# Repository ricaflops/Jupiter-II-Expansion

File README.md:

# Jupiter-II Expansion
An Expansion board for the [Jupiter-II](https://github.com/ricaflops/Jupiter-II) computer

## Expands Jupiter-II with
- Video color: 16 colors, RGB output
- Programmable Sound Generator
- 128K RAM: paged
- 16K ROM: FORTH vocabulary extension
- Serial Interface

## FORTH code examples

### Colors
```
CYAN BORDER ( Change screen border color )
WHITE PAPER ( Set char background color )
BLUE DARK INK ( Set char foreground color ) 

: COLORBAR
  CLS 10 8 AT 16 0
  DO
   I INK 144 EMIT
  LOOP 
  BLACK INK
  ;
COLORBAR ( Show a colorfull bar )
```

### Memory/Screen/Font Paging
```
0 FONT  ( select alternative character set )
1 FONT  ( select original character set )

0 SCREEN ( select screen page 0 )
1 SCREEN ( select screen page 1 )

0 MPAGE ( select memory page 0 )
3 MPAGE ( select memory page 3 )
```

### Sounds
```
: PING
  200 0 PSG!
  254 7 PSG!
  16 8 PSG!
  20 12 PSG!
  1 13 PSG!
;

: SHOT
  8 6 PSG!
  247 7 PSG!
  16 8 PSG!
  20 12 PSG!
  1  13 PSG!
;
```

### Serial Comm Port
8 data bits, 1 stop bit, no parity.
```
CREATE BUFFER 256 ALLOT ( Create and Allocate a memory space to work )
: CLRBUF BUFFER 256 32 FILL ; ( Clear Buffer )
: PRTBUF CR 256 0 DO BUFFER I + EMIT LOOP CR ; ( Print Buffer )

9600 BAUD     ( set communication baud rate )
CLRBUF        ( Clear Buffer )
BUFFER 256 RX ( Receive 256 bytes from serial line )
PRTBUF        ( View received data )
BUFFER 256 TX ( Transmit 256 bytes over serial line )
```
*Note: use Space key to abort communication if needed*

# Extra FORTH vocabulary
The extended vocabulary is copied from XROM to a unused 1K RAM area at $3000-$33FF of Jupiter-II during initialization.
That allows safe memory paging while keeping the extra Words accessible.

### Standard FORTH words

```
COUNT ( addr -- addr+1 c )  Extract String length
+! ( n addr -- )  Add 'n' to 'addr' variable
? ( addr -- )  Print variable value
CMOVE ( addr1 addr2 n -- )  Copy 'n' bytes from 'addr1' to 'addr2'
FILL  ( addr n c -- )  Fill 'n' bytes with 'c' starting from 'addr'
DEPTH ( -- n )  Data Stack Depth
HEX   ( -- )  Set numeric base to Hexadecimal
```

### Programmable Sound Generator

```
PSG! ( c reg -- ) Write 'c' to PSG register 'reg'
PSG@ ( reg -- c ) Read PSG register 'reg' contents
```

### Colors

```
BORDER ( c -- ) Set screen BORDER to color 'c' , 0 to 15
INK    ( c -- ) Set character INK to color 'c' , 0 to 15
PAPER  ( c -- ) Set character PAPER to color 'c' , 0 to 15
BLACK  ( -- c ) Stack color code for Black
GREY   ( -- c ) Stack color code for Grey
BLUE   ( -- c ) Stack color code for Blue
GREEN  ( -- c ) Stack color code for Green
CYAN   ( -- c ) Stack color code for Cyan
RED    ( -- c ) Stack color code for Red
PURPLE ( -- c ) Stack color code for Purple
YELLOW ( -- c ) Stack color code for Yellow
WHITE  ( -- c ) Stack color code for White
DARK   ( c1 -- c2 ) Change color code on stack to a darker tone
```

### Serial Communication
8 data bits, 1 stop bit, no parity.

```
BAUD ( n --  )  Set UART to Baud rate 'n'
TX ( addr n --  )  Transmit 'n' bytes starting from 'addr' to serial line
RX ( addr n --  )  Receive 'n' bytes from serial line to memory 'addr'
```

Avoid transfering to/from video RAM using video circuit priority addressing. That prevents transfer speeds above 1200 bauds.
- Video RAM from $2400 to $27FF. Use mirror addressing $2000 to $23FF instead (CPU priority).
- Character Genrator RAM from $2C00 to $2FFF. Use mirror addressing $2800 to $2BFF instead (CPU priority).

*Note: Character Generator RAM is write only*

### Memory Paging
```
MPAGE  ( c -- ) Select memory page 'c' , 0 to 3
SCREEN ( c -- ) Select Screen page 'c' , 0 or 1
FONT   ( c -- ) Select character set 'c' , 0 or 1
```

*Note: System resets to page 3*

## Programmable Sound Generator Registers

```
   bits: 76543210 76543210
  R1 R0: ----tttt tttttttt : Tone generator A period (12-bits) 0-4095
  R3 R2: ----tttt tttttttt : Tone generator B period (12-bits) 0-4095
  R5 R4: ----tttt tttttttt : Tone generator C period (12-bits) 0-4095
     R6:          ---ttttt : Noise generator period  (5-bits)  0-31
     R7:          ppcbaCBA : I/O port and sound channel enablers
     R8:          ---Mvvvv : Channel A Volume (v) and Envelope Mode (M)
     R9:          ---Mvvvv : Channel B Volume (v) and Envelope Mode (M)
    R10:          ---Mvvvv : Channel C Volume (v) and Envelope Mode (M)
R12 R11: tttttttt tttttttt : Envelope period (16-bits) 0-65535
    R13:          ----calh : Envelope Shape: Continue (c), Attack (a), Alternate(l), Hold (h)
    R14:          dddddddd : I/O Port-A data
    R15:          dddddddd : I/O Port-B data
```

**R0..R6**: Tone and Noise Period (Frequency) settings<br/>
> t = 203125 / f , where f is the desirable frequency in Hz<br/>
> Tone Range: 49.6 Hz to 203.1 kHz (0..4095)<br/>
> Noise Range: 6.55 kHz to 293.1 kHz (0..31)<br/>

**R7**: Tone and Noise Mixer and I/O Ports direction<br/>
- bit0: when 0 enables tone A on channel A, 1 disables it
- bit1: when 0 enables tone B on channel B, 1 disables it
- bit2: when 0 enables tone C on channel C, 1 disables it
- bit3: when 0 enables Noise on channel A, 1 disables it
- bit4: when 0 enables Noise on channel B, 1 disables it
- bit5: when 0 enables Noise on channel C, 1 disables it
- bit6: when 0 set digital Port-A as input, 1 set it as output
- bit7: when 0 set digital Port-B as input, 1 set it as output<br/>

**R8..R10**: Channel volume<br/>
- bit4  : when 0 volume is fixed, when 1 volume is Envelope controlled
- bit3-0: Fixed volume value (0-31)<br/>

**R11, R12**: Envelope period<br/>
> t = s / 78.769e-6 , where s is the desirable period in seconds<br/>
> Period range: 78.8 us to 5.16 seconds<br/>

**R13**: Envelope Shape combination<br/>
- bit3: Continue: when 1 follows Hold setting, when 0 resets down after one cycle
- bit2: Attack: when 1 attack ramps up, when 0 ramps down
- bit1: Alternate: when 1 envelope shape reverses on each cycle (up/down)
- bit0: Hold: when 1 limits to one cycle and sustain final value<br/>

**R14, R15**: Digital I/O Port data<br/>
- Port A (register 14) controls PAPER and INK colors
- Port B (register 15) controls BORDER color and paging<br/>

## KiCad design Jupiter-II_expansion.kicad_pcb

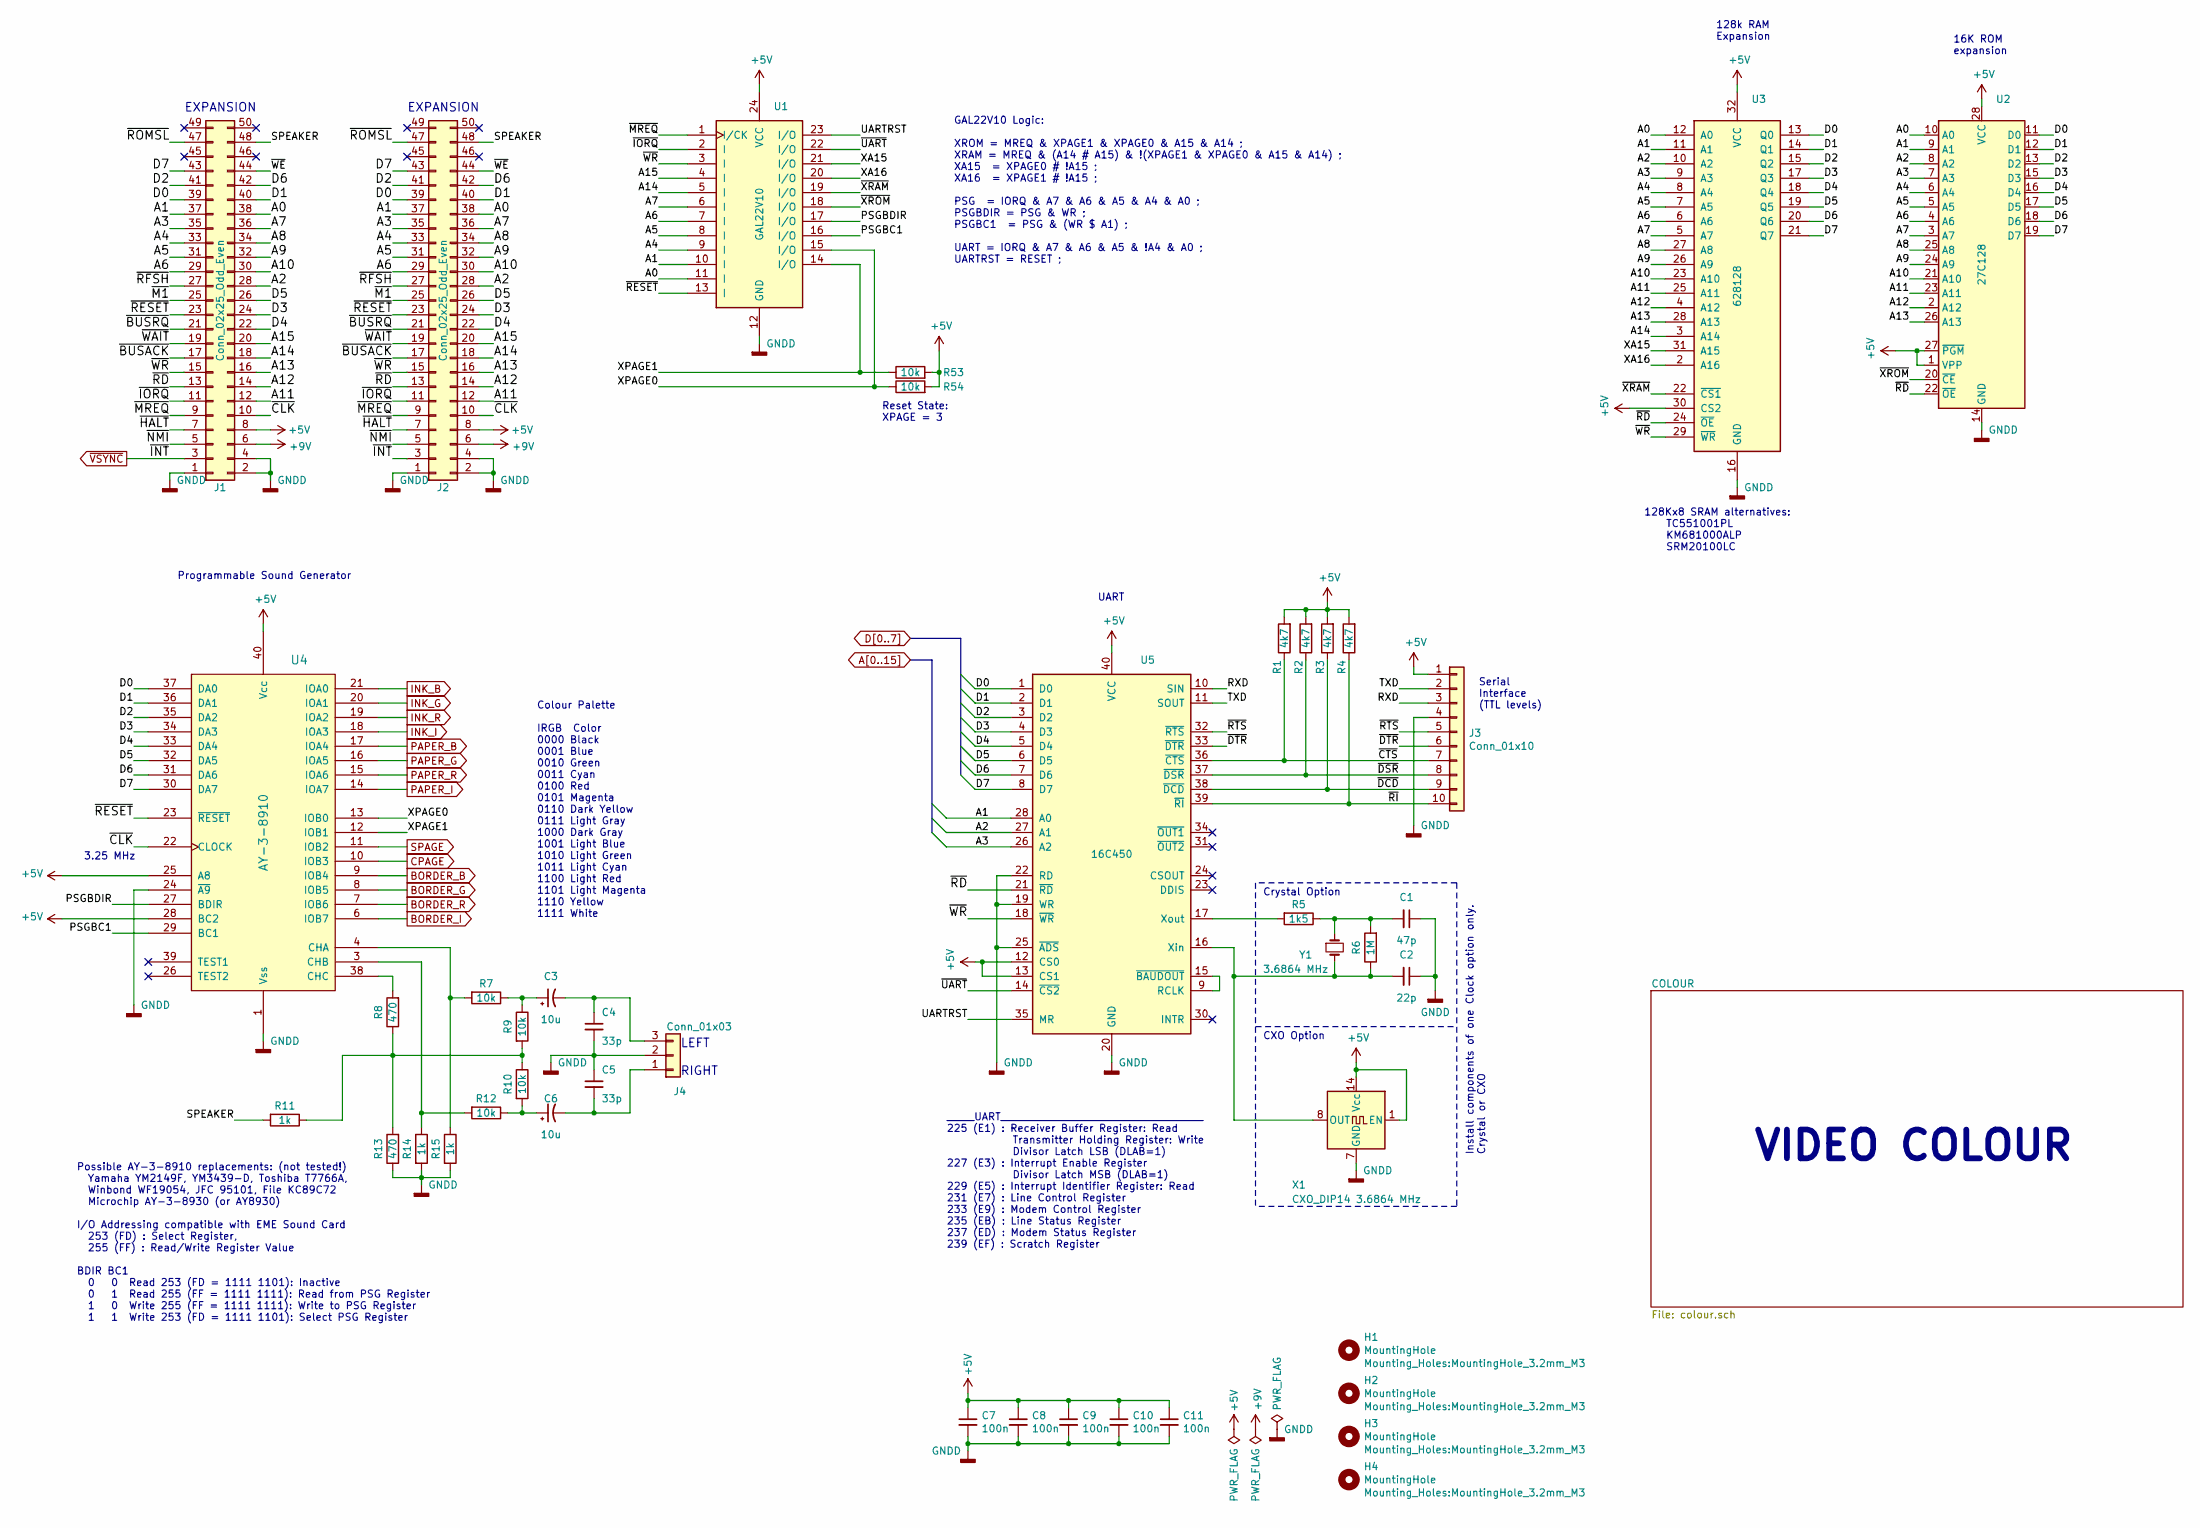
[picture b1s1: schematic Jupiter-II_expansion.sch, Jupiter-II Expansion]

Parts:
C1: 47p; C_0805_2012Metric_Pad1.15x1.40mm_HandSolder
C2: 22p; C_0805_2012Metric_Pad1.15x1.40mm_HandSolder
C3, C6: 10u; CP_EIA-6032-15_Kemet-U_Pad2.25x2.35mm_HandSolder
C4, C5: 33p; C_0805_2012Metric_Pad1.15x1.40mm_HandSolder
C7, C8, C9, C10, C11: 100n; C_Rect_L7.0mm_W2.5mm_P5.00mm
H1, H2, H3, H4: MountingHole; MountingHole_3.2mm_M3
J1: Conn_02x25_Odd_Even; PinHeader_2x25_P2.54mm_Vertical
J2: Conn_02x25_Odd_Even; PinSocket_2x25_P2.54mm_Vertical
J3: Conn_01x10; Molex_KK-254_AE-6410-10A_1x10_P2.54mm_Vertical
J4: Conn_01x03; Molex_KK-254_AE-6410-03A_1x03_P2.54mm_Vertical
R1, R2, R3, R4: 4k7; R_0805_2012Metric_Pad1.15x1.40mm_HandSolder
R5: 1k5; R_0805_2012Metric_Pad1.15x1.40mm_HandSolder
R6: 1M; R_0805_2012Metric_Pad1.15x1.40mm_HandSolder
R7, R9, R10, R12, R53, R54: 10k; R_0805_2012Metric_Pad1.15x1.40mm_HandSolder
R8, R13: 470; R_0805_2012Metric_Pad1.15x1.40mm_HandSolder
R11, R14, R15: 1k; R_0805_2012Metric_Pad1.15x1.40mm_HandSolder
U1: GAL22V10; DIP-24_W7.62mm_Socket
U2: 27C128; DIP-28_W15.24mm
U3: 628128; DIP-32_W15.24mm
U4: AY-3-8910; DIP-40_W15.24mm_Socket
U5: 16C450; DIP-40_W15.24mm_Socket
X1: CXO_DIP14 3.6864 MHz; Oscillator_DIP-14
Y1: 3.6864 MHz; Crystal_HC18-U_Vertical

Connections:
+5V: C7.1, C8.1, C9.1, C10.1, C11.1, J1.8, J2.8, J3.1, R1.2, R2.2, R3.2, R4.2, R53.2, R54.2, U1.24 (VCC), U2.1 (VPP), U2.27 (~PGM), U2.28 (VCC), U3.30 (CS2), U3.32 (VCC), U4.25 (A8), U4.28 (BC2), U4.40 (Vcc), U5.12 (CS0), U5.13 (CS1), U5.40 (VCC), X1.1 (EN), X1.14 (Vcc); also elsewhere on the board
+9V: J1.6, J2.6
/PSGBC1: U1.16 (I/O), U4.29 (BC1)
/PSGBDIR: U1.17 (I/O), U4.27 (BDIR)
/RXD: J3.3, U5.10 (SIN)
/SPEAKER: J1.48, J2.48, R11.2
/TXD: J3.2, U5.11 (SOUT)
/UARTRST: U1.23 (I/O), U5.35 (MR)
/XA15: U1.21 (I/O), U3.31 (A15)
/XA16: U1.20 (I/O), U3.2 (A16)
/XPAGE0: R54.1, U1.15 (I/O), U4.13 (IOB0)
/XPAGE1: R53.1, U1.14 (I/O), U4.12 (IOB1)
/~BUSACK: J1.17, J2.17
/~BUSRQ: J1.21, J2.21
/~CLK: J1.10, J2.10, U4.22 (CLOCK)
/~CTS: J3.7, R1.1, U5.36 (~CTS)
/~DCD: J3.9, R3.1, U5.38 (~DCD)
/~DSR: J3.8, R2.1, U5.37 (~DSR)
/~DTR: J3.6, U5.33 (~DTR)
/~HALT: J1.7, J2.7
/~IORQ: J1.11, J2.11, U1.2 (I)
/~M1: J1.25, J2.25
/~MREQ: J1.9, J2.9, U1.1 (I/CK)
/~NMI: J1.5, J2.5
/~RD: J1.13, J2.13, U2.22 (~OE), U3.24 (~OE), U5.21 (~RD)
/~RESET: J1.23, J2.23, U1.13 (I), U4.23 (~RESET)
/~RFSH: J1.27, J2.27
/~RI: J3.10, R4.1, U5.39 (~RI)
/~ROMSL: J1.47, J2.47
/~RTS: J3.5, U5.32 (~RTS)
/~UART: U1.22 (I/O), U5.14 (~CS2)
/~WAIT: J1.19, J2.19
/~WE: J1.44, J2.44
/~WR: J1.15, J2.15, U1.3 (I), U3.29 (~WR), U5.18 (~WR)
/~XRAM: U1.19 (I/O), U3.22 (~CS1)
/~XROM: U1.18 (I/O), U2.20 (~CE)
A0: J1.38, J2.38, U1.11 (I), U2.10 (A0), U3.12 (A0)
A1: J1.37, J2.37, U1.10 (I), U2.9 (A1), U3.11 (A1), U5.28 (A0)
A2: J1.28, J2.28, U2.8 (A2), U3.10 (A2), U5.27 (A1)
A3: J1.35, J2.35, U2.7 (A3), U3.9 (A3), U5.26 (A2)
A4: J1.33, J2.33, U1.9 (I), U2.6 (A4), U3.8 (A4)
A5: J1.31, J2.31, U1.8 (I), U2.5 (A5), U3.7 (A5)
A6: J1.29, J2.29, U1.7 (I), U2.4 (A6), U3.6 (A6)
A7: J1.36, J2.36, U1.6 (I), U2.3 (A7), U3.5 (A7)
A8: J1.34, J2.34, U2.25 (A8), U3.27 (A8)
A9: J1.32, J2.32, U2.24 (A9), U3.26 (A9)
A10: J1.30, J2.30, U2.21 (A10), U3.23 (A10)
A11: J1.12, J2.12, U2.23 (A11), U3.25 (A11)
A12: J1.14, J2.14, U2.2 (A12), U3.4 (A12)
A13: J1.16, J2.16, U2.26 (A13), U3.28 (A13)
A14: J1.18, J2.18, U1.5 (I), U3.3 (A14)
A15: J1.20, J2.20, U1.4 (I)
BORDER_B: U4.9 (IOB4); also elsewhere on the board
BORDER_G: U4.8 (IOB5); also elsewhere on the board
BORDER_I: U4.6 (IOB7); also elsewhere on the board
BORDER_R: U4.7 (IOB6); also elsewhere on the board
CPAGE: U4.10 (IOB3); also elsewhere on the board
D0: J1.39, J2.39, U2.11 (D0), U3.13 (Q0), U4.37 (DA0), U5.1 (D0)
D1: J1.40, J2.40, U2.12 (D1), U3.14 (Q1), U4.36 (DA1), U5.2 (D1)
D2: J1.41, J2.41, U2.13 (D2), U3.15 (Q2), U4.35 (DA2), U5.3 (D2)
D3: J1.24, J2.24, U2.15 (D3), U3.17 (Q3), U4.34 (DA3), U5.4 (D3)
D4: J1.22, J2.22, U2.16 (D4), U3.18 (Q4), U4.33 (DA4), U5.5 (D4)
D5: J1.26, J2.26, U2.17 (D5), U3.19 (Q5), U4.32 (DA5), U5.6 (D5)
D6: J1.42, J2.42, U2.18 (D6), U3.20 (Q6), U4.31 (DA6), U5.7 (D6)
D7: J1.43, J2.43, U2.19 (D7), U3.21 (Q7), U4.30 (DA7), U5.8 (D7)
GNDD: C1.1, C2.1, C4.2, C5.1, C7.2, C8.2, C9.2, C10.2, C11.2, J1.1, J1.2, J1.4, J2.1, J2.2, J2.4, J3.4, J4.2, R13.1, R14.2, R15.2, U1.12 (GND), U2.14 (GND), U3.16 (GND), U4.1 (Vss), U4.24 (~A9), U5.19 (WR), U5.20 (GND), U5.22 (RD), U5.25 (~ADS), X1.7 (GND); also elsewhere on the board
INK_B: U4.21 (IOA0); also elsewhere on the board
INK_G: U4.20 (IOA1); also elsewhere on the board
INK_I: U4.18 (IOA3); also elsewhere on the board
INK_R: U4.19 (IOA2); also elsewhere on the board
unnamed: C1.2, R5.1, R6.2, Y1.1
unnamed: C2.2, R6.1, U5.16 (Xin), X1.8 (OUT), Y1.2
unnamed: C3.1, R7.1, R9.1
unnamed: C3.2, C4.1, J4.3
unnamed: C5.2, C6.2, J4.1
unnamed: C6.1, R10.2, R12.1
unnamed: R5.2, U5.17 (Xout)
unnamed: R8.2, U4.38 (CHC)
unnamed: R8.1, R9.2, R10.1, R11.1, R13.2
unnamed: R12.2, R14.1, U4.3 (CHB)
unnamed: R7.2, R15.1, U4.4 (CHA)
unnamed: U5.9 (RCLK), U5.15 (~BAUDOUT)
PAPER_B: U4.17 (IOA4); also elsewhere on the board
PAPER_G: U4.16 (IOA5); also elsewhere on the board
PAPER_I: U4.14 (IOA7); also elsewhere on the board
PAPER_R: U4.15 (IOA6); also elsewhere on the board
SPAGE: U4.11 (IOB2); also elsewhere on the board
~VSYNC: J1.3, J2.3

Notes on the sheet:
Programmable Sound Generator
Possible AY-3-8910 replacements: (not tested!) Yamaha YM2149F, YM3439-D, Toshiba T7766A, Winbond WF19054, JFC 95101, File KC89C72 Microchip AY-3-8930 (or AY8930) I/O Addressing compatible with EME Sound Card 253 (FD) : Select Register, 255 (FF) : Read/Write Register Value BDIR BC1 0 0 Read 253 (FD 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
LEFT RIGHT
GAL22V10 Logic: XROM = MREQ & XPAGE1 & XPAGE0 & A15 & A14 ; XRAM = MREQ & (A14 # A15) & !(XPAGE1 & XPAGE0 & A15 & A14) ; XA15 = XPAGE0 # !A15 ; XA16 = XPAGE1 # !A15 ; PSG = IORQ & A7 & A6 & A5 & A4 & A0 ; PSGBDIR = PSG & WR ; PSGBC1 = PSG & (WR $ A1) ; UART = IORQ & A7 & A6 & A5 & !A4 & A0 ; UARTRS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
128k RAM Expansion
16K ROM expansion
3.25 MHz
EXPANSION
VIDEO COLOUR
UART
CXO Option
Crystal Option
Serial Interface (TTL levels)
Install components of one Clock option only. Crystal or CXO
_____UART_____________________________________ 225 (E1) : Receiver Buffer Register: Read Transmitter Holding Register: Write Divisor Latch LSB (DLAB=1) 227 (E3) : Interrupt Enable Register Divisor Latch MSB (DLAB=1) 229 (E5) : Interrupt Identifier Register: Read 231 (E7) : Line Control Register 233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
128Kx8 SRAM alternatives: TC551001PL KM681000ALP SRM20100LC
Colour Palette IRGB Color 0000 Black 0001 Blue 0010 Green 0011 Cyan 0100 Red 0101 Magenta 0110 Dark Yellow 0111 Light Gray 1000 Dark Gray 1001 Light Blue 1010 Light Green 1011 Light Cyan 1100 Light Red 1101 Light Magenta 1110 Yellow 1111 White
Reset State: XPAGE = 3

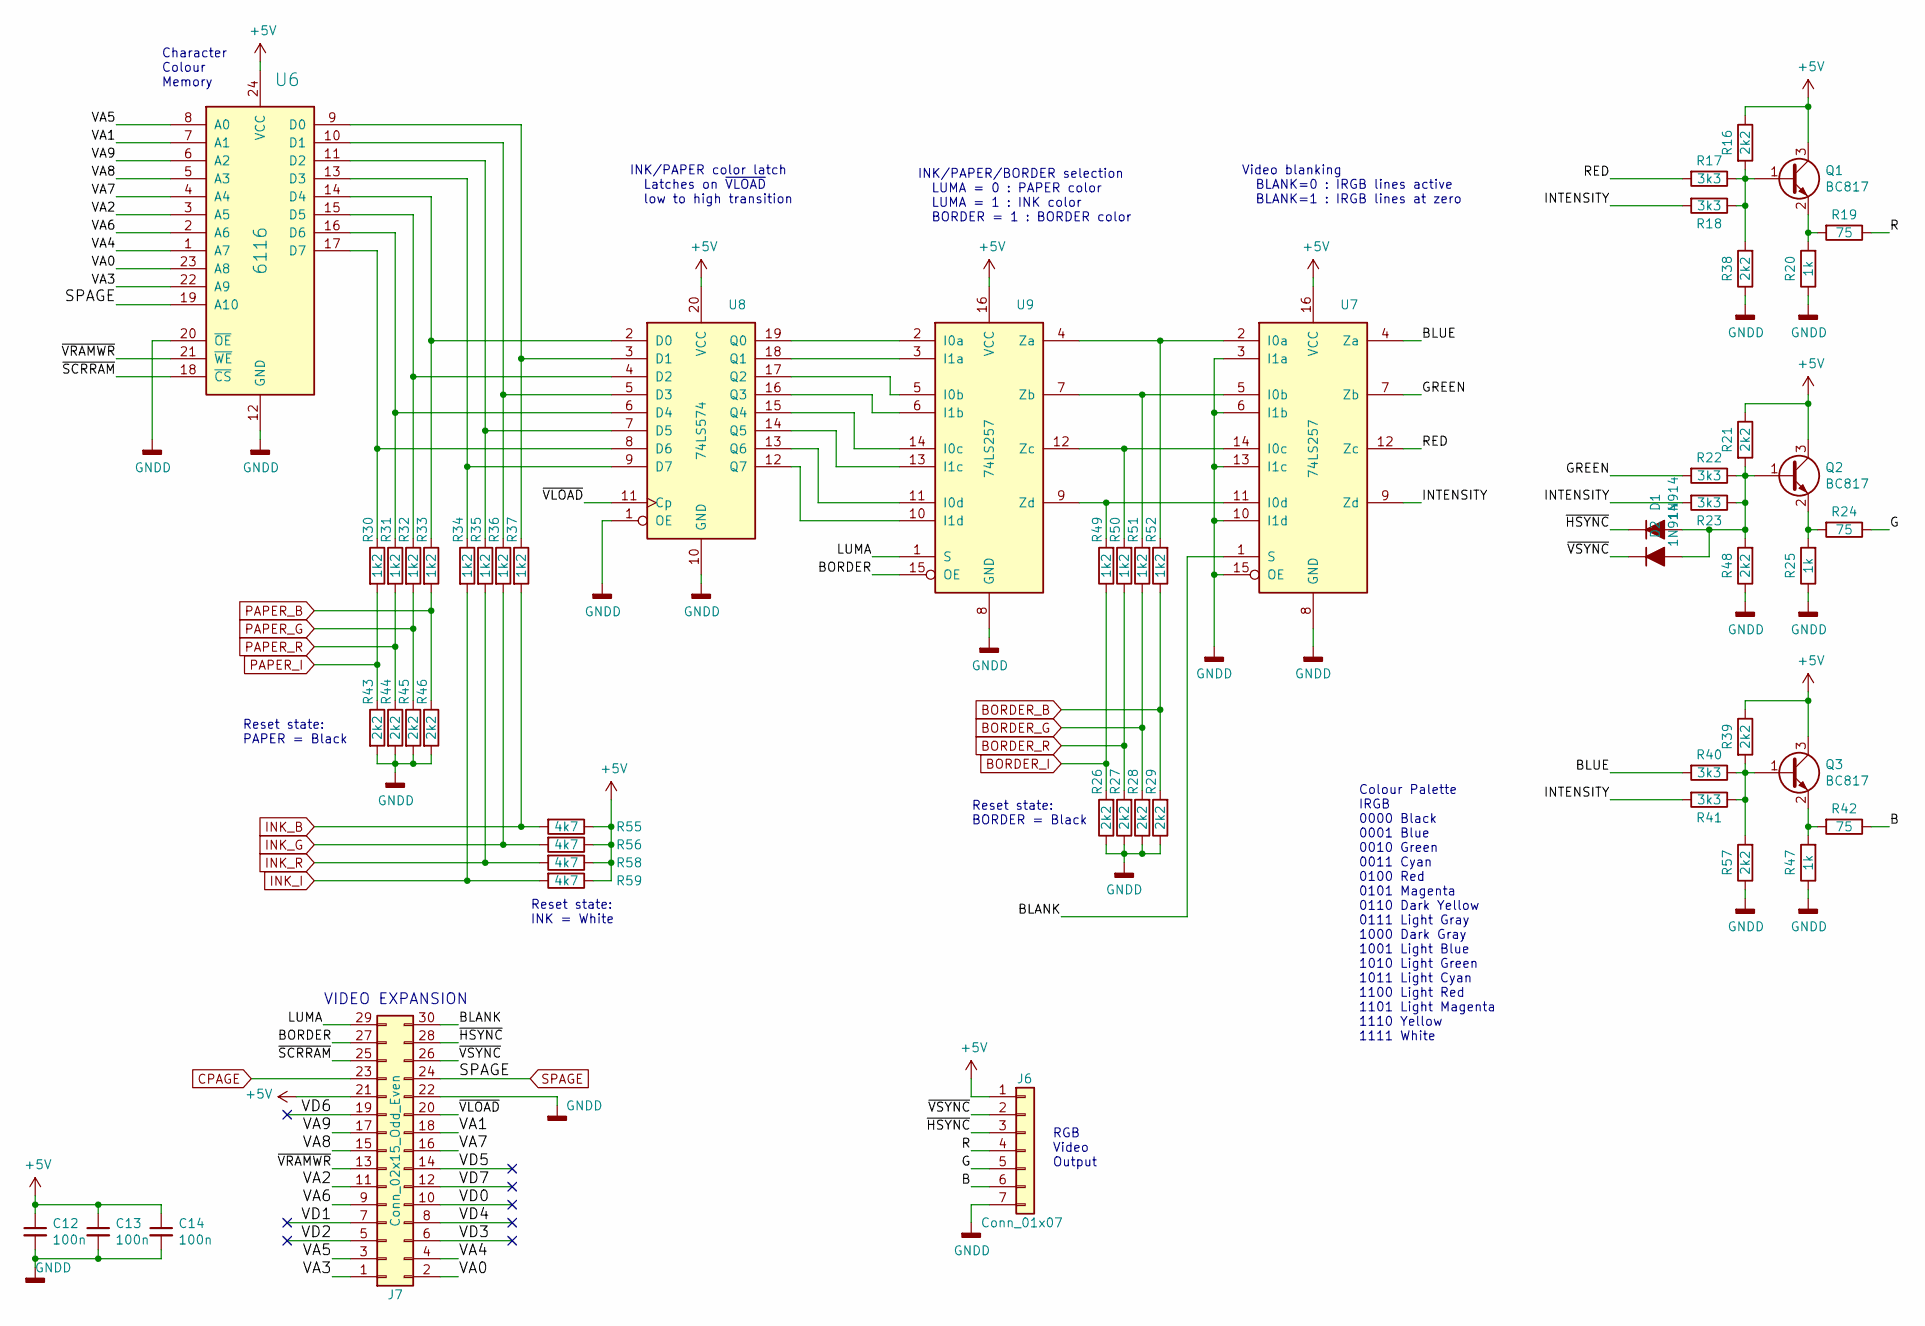
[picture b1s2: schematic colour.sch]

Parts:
C12, C13, C14: 100n; C_Rect_L7.0mm_W2.5mm_P5.00mm
D1, D2: 1N914; D_DO-35_SOD27_P7.62mm_Horizontal
J6: Conn_01x07; Molex_KK-254_AE-6410-07A_1x07_P2.54mm_Vertical
J7: Conn_02x15_Odd_Even; PinHeader_2x15_P2.54mm_Vertical
Q1, Q2, Q3: BC817; SOT-23
R16, R21, R26, R27, R28, R29, R38, R39, R43, R44, R45, R46, R48, R57: 2k2; R_0805_2012Metric_Pad1.15x1.40mm_HandSolder
R17, R18, R22, R23, R40, R41: 3k3; R_0805_2012Metric_Pad1.15x1.40mm_HandSolder
R19, R24, R42: 75; R_0805_2012Metric_Pad1.15x1.40mm_HandSolder
R20, R25, R47: 1k; R_0805_2012Metric_Pad1.15x1.40mm_HandSolder
R30, R31, R32, R33, R34, R35, R36, R37, R49, R50, R51, R52: 1k2; R_0805_2012Metric_Pad1.15x1.40mm_HandSolder
R55, R56, R58, R59: 4k7; R_0805_2012Metric_Pad1.15x1.40mm_HandSolder
U6: 6116; DIP-24_W15.24mm
U7, U9: 74LS257; DIP-16_W7.62mm
U8: 74LS574; DIP-20_W7.62mm

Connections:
+5V: C12.1, C13.1, C14.1, J6.1, J7.21, Q1.3 (C), Q2.3 (C), Q3.3 (C), R16.1, R21.1, R39.1, R55.1, R56.1, R58.1, R59.1, U6.24 (VCC), U7.16 (VCC), U8.20 (VCC), U9.16 (VCC); also elsewhere on the board
/COLOUR/B: J6.6, R42.1
/COLOUR/BLANK: J7.30, U7.1 (S)
/COLOUR/BLUE: R40.2, U7.4 (Za)
/COLOUR/BORDER: J7.27, U9.15 (OE)
/COLOUR/G: J6.5, R24.1
/COLOUR/GREEN: R22.2, U7.7 (Zb)
/COLOUR/INTENSITY: R18.2, R23.2, R41.2, U7.9 (Zd)
/COLOUR/LUMA: J7.29, U9.1 (S)
/COLOUR/R: J6.4, R19.1
/COLOUR/RED: R17.2, U7.12 (Zc)
/COLOUR/VA0: J7.2, U6.23 (A8)
/COLOUR/VA1: J7.18, U6.7 (A1)
/COLOUR/VA2: J7.11, U6.3 (A5)
/COLOUR/VA3: J7.1, U6.22 (A9)
/COLOUR/VA4: J7.4, U6.1 (A7)
/COLOUR/VA5: J7.3, U6.8 (A0)
/COLOUR/VA6: J7.9, U6.2 (A6)
/COLOUR/VA7: J7.16, U6.4 (A4)
/COLOUR/VA8: J7.15, U6.5 (A3)
/COLOUR/VA9: J7.17, U6.6 (A2)
/COLOUR/VD0: J7.10
/COLOUR/VD1: J7.7
/COLOUR/VD2: J7.5
/COLOUR/VD3: J7.6
/COLOUR/VD4: J7.8
/COLOUR/VD5: J7.14
/COLOUR/VD6: J7.19
/COLOUR/VD7: J7.12
/COLOUR/~HSYNC: D1.1 (K), J6.3, J7.28
/COLOUR/~SCRRAM: J7.25, U6.18 (~CS)
/COLOUR/~VLOAD: J7.20, U8.11 (Cp)
/COLOUR/~VRAMWR: J7.13, U6.21 (~WE)
/COLOUR/~VSYNC: D2.1 (K), J6.2, J7.26
BORDER_B: R29.2, R52.1; also elsewhere on the board
BORDER_G: R28.2, R51.1; also elsewhere on the board
BORDER_I: R26.2, R49.1; also elsewhere on the board
BORDER_R: R27.2, R50.1; also elsewhere on the board
CPAGE: J7.23; also elsewhere on the board
GNDD: C12.2, C13.2, C14.2, J6.7, J7.22, R20.1, R25.1, R26.1, R27.1, R28.1, R29.1, R38.1, R43.2, R44.2, R45.2, R46.2, R47.1, R48.1, R57.1, U6.12 (GND), U6.20 (~OE), U7.3 (I1a), U7.6 (I1b), U7.8 (GND), U7.10 (I1d), U7.13 (I1c), U7.15 (OE), U8.1 (OE), U8.10 (GND), U9.8 (GND); also elsewhere on the board
INK_B: R37.2, R55.2; also elsewhere on the board
INK_G: R36.2, R56.2; also elsewhere on the board
INK_I: R34.2, R59.2; also elsewhere on the board
INK_R: R35.2, R58.2; also elsewhere on the board
unnamed: D1.2 (A), D2.2 (A), Q2.1 (B), R21.2, R22.1, R23.1, R48.2
unnamed: Q1.1 (B), R16.2, R17.1, R18.1, R38.2
unnamed: Q1.2 (E), R19.2, R20.2
unnamed: Q2.2 (E), R24.2, R25.2
unnamed: Q3.1 (B), R39.2, R40.1, R41.1, R57.2
unnamed: Q3.2 (E), R42.2, R47.2
unnamed: R30.1, U6.17 (D7), U8.8 (D6)
unnamed: R31.1, U6.16 (D6), U8.6 (D4)
unnamed: R32.1, U6.15 (D5), U8.4 (D2)
unnamed: R33.1, U6.14 (D4), U8.2 (D0)
unnamed: R34.1, U6.13 (D3), U8.9 (D7)
unnamed: R35.1, U6.11 (D2), U8.7 (D5)
unnamed: R36.1, U6.10 (D1), U8.5 (D3)
unnamed: R37.1, U6.9 (D0), U8.3 (D1)
unnamed: R49.2, U7.11 (I0d), U9.9 (Zd)
unnamed: R50.2, U7.14 (I0c), U9.12 (Zc)
unnamed: R51.2, U7.5 (I0b), U9.7 (Zb)
unnamed: R52.2, U7.2 (I0a), U9.4 (Za)
unnamed: U8.12 (Q7), U9.10 (I1d)
unnamed: U8.13 (Q6), U9.11 (I0d)
unnamed: U8.14 (Q5), U9.13 (I1c)
unnamed: U8.15 (Q4), U9.14 (I0c)
unnamed: U8.16 (Q3), U9.6 (I1b)
unnamed: U8.17 (Q2), U9.5 (I0b)
unnamed: U8.18 (Q1), U9.3 (I1a)
unnamed: U8.19 (Q0), U9.2 (I0a)
PAPER_B: R33.2, R46.1; also elsewhere on the board
PAPER_G: R32.2, R45.1; also elsewhere on the board
PAPER_I: R30.2, R43.1; also elsewhere on the board
PAPER_R: R31.2, R44.1; also elsewhere on the board
SPAGE: J7.24, U6.19 (A10); also elsewhere on the board

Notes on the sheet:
INK/PAPER color latch Latches on ~VLOAD~ low to high transition
Character Colour Memory
Colour Palette IRGB 0000 Black 0001 Blue 0010 Green 0011 Cyan 0100 Red 0101 Magenta 0110 Dark Yellow 0111 Light Gray 1000 Dark Gray 1001 Light Blue 1010 Light Green 1011 Light Cyan 1100 Light Red 1101 Light Magenta 1110 Yellow 1111 White
INK/PAPER/BORDER selection LUMA = 0 : PAPER color LUMA = 1 : INK color BORDER = 1 : BORDER color
Reset state: PAPER = Black
Reset state: INK = White
VIDEO EXPANSION
Reset state: BORDER = Black
Video blanking BLANK=0 : IRGB lines active BLANK=1 : IRGB lines at zero
RGB Video Output

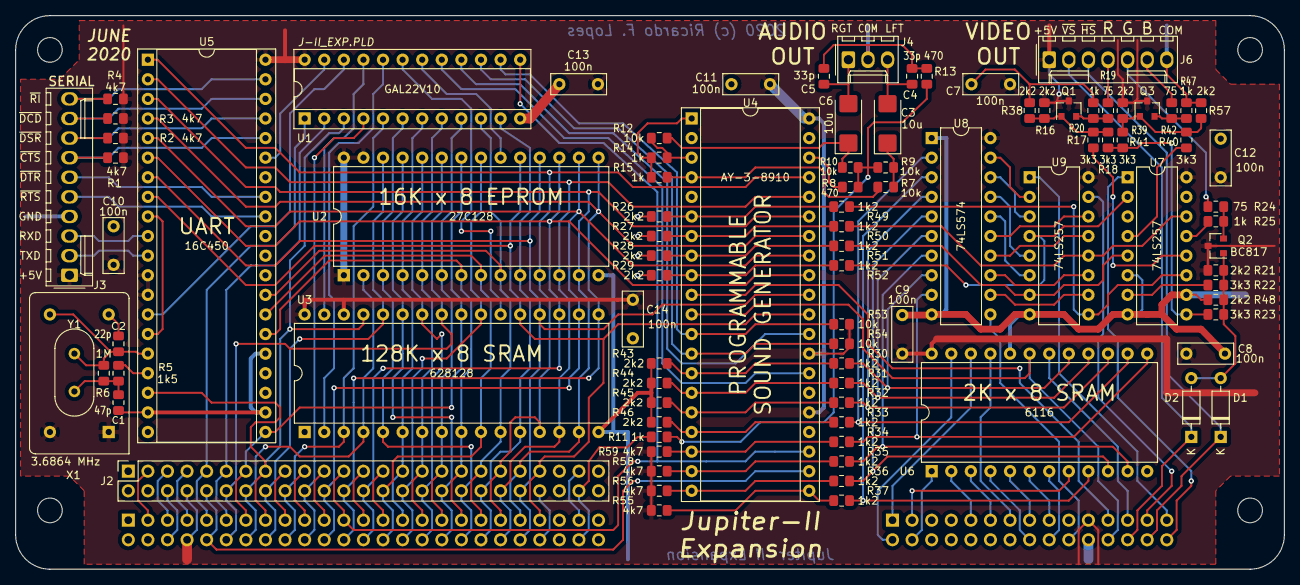
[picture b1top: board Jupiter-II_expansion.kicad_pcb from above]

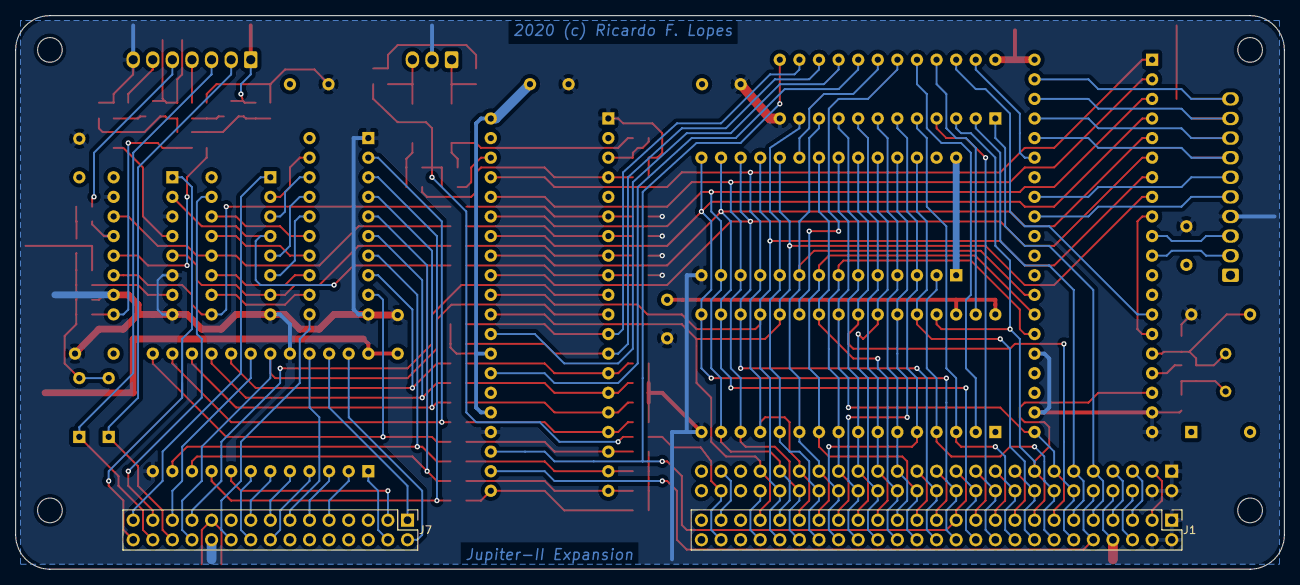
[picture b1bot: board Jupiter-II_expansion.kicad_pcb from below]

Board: 2 copper layers, 164.5 x 71.8 mm, 99 parts (2 on the bottom side), 139 nets.

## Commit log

2020-06-22 Create LICENSE
2020-08-02 First working version
2020-08-02 First working version
    Hardware validation
2020-08-02 Delete file5E8292A5.pro
    Obsolete
2020-08-03 Added some codes to try
2020-08-03 Added memory map
2020-08-06 Text corrections
2020-08-13 List Expanded FORTH vocabulary
2020-08-13 Corrected missing connections on XROM
    Corrected missing connections on XROM pins 1 and 27
2020-08-16 First working xROM
2020-08-16 v1.0
2020-08-16 Project Complete
2020-08-22 Improved char font
2020-10-06 Added missing library
    Added missing library and PDF schematic
2026-02-05 Cosmetics
